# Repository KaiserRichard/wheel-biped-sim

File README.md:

# Wheel-biped simulation

A wheel-legged biped robot built three ways before any motor turns: **MuJoCo** physics, a **MATLAB Simscape Multibody** model, and the robot's own **KiCad 9 electronics**. Two five-bar legs each end in a driven wheel; the robot balances like an inverted pendulum, drives, turns, changes height and jumps.

*Simulation only: the CAD robot at an assumed 8.5 kg clearing an 8 cm obstacle in MuJoCo.*

This project builds on Trần Nguyên Bình's [DM-jump](https://github.com/nguyenbinh-shark/DM-jump) (MIT) and [dmBots/wheel-legged](https://github.com/dmBots/wheel-legged) (MIT). It is a personal refactor and extension: the concept and scenarios come from that work, and the code here was rewritten and reorganized. CAD meshes are not included. AI coding tools were used heavily in building it; the author reviewed and is responsible for all content. See [NOTICE.md](NOTICE.md).

## Simulation

Click any clip for the full MP4. All clips are played back from simulation runs, not footage of a real robot.

<table>
<tr>
<td align="center"><br>Simscape Multibody: full 16 s mission</td>
<td align="center"><br>PPO vs LQR: recovery from a 40° tilt</td>
<td align="center"><br>CAD model in MuJoCo</td>
</tr>
<tr>
<td align="center"><br>Stand and reject a push</td>
<td align="center"><br>Drive</td>
<td align="center"><br>Turn</td>
</tr>
<tr>
<td align="center"><br>Change leg height</td>
<td align="center"><br>Jump</td>
<td align="center"><br>Clear an 8 cm obstacle</td>
</tr>
<tr>
<td align="center"><br>8.5 kg: one-sided ramp</td>
<td align="center"><br>8.5 kg: 0.245 m drop</td>
<td align="center"><br>2 ms extra delay: the first controller falls</td>
</tr>
<tr>
<td align="center"><br>Firmware in the loop: <a href="docs/studies/figure-8-path-tracking.md">figure-8 path tracking</a></td>
<td align="center"><br>Firmware in the loop: <a href="docs/studies/lateral-push-low-friction.md">30 N push on a slippery floor</a></td>
<td></td>
</tr>
<tr>
<td align="center"><br>Firmware in the loop: <a href="docs/studies/push-window.md">push window, worst pitch 9.3° → 1.4°</a></td>
<td align="center"><br>Firmware in the loop: <a href="docs/studies/grip-aware-braking.md">grip-aware braking, falls 37/96 → 0/96</a></td>
<td></td>
</tr>
</table>

The full clip list, the MATLAB figures and the control story are in [docs/DETAILS.md](docs/DETAILS.md).

## Electronics

Three boards designed in KiCad 9 for a 6S battery (18.0–25.2 V). Design only: not fabricated or powered. Sources, schematic PDFs and check reports: [hardware/](hardware/README.md).

<table>
<tr>
<th>6S power and monitor board</th>
<th>STM32H723 control board</th>
<th>Motor power board</th>
</tr>
<tr>
<td align="center"></td>
<td align="center"></td>
<td align="center"></td>
</tr>
<tr>
<td align="center"></td>
<td align="center"></td>
<td align="center"></td>
</tr>
<tr>
<td>Input protection, 5 V buck rails for the Raspberry Pi and auxiliary loads, power monitoring and e-stop status. KiCad 9, ERC/DRC clean.</td>
<td>MCU with three CAN buses to the joint and wheel motors, USB to the Pi and an IMU sensor on SPI. KiCad 9, ERC/DRC clean.</td>
<td>Contactors, precharge, brake chopper and safety latch for the motor bus. KiCad 9, rev 2 schematic ERC clean; views are of the earlier layout.</td>
</tr>
</table>

Renders show archived layouts; the newest power and control revisions are listed in [hardware/README.md](hardware/README.md).

## What's inside

| Area | What it is | Read more |
| --- | --- | --- |
| MuJoCo model | Five-bar kinematics, controller and scenarios with a CPU parity test | [docs/PROJECT.md](docs/PROJECT.md) |
| Simscape model | Multibody robot with contact, six drives on a battery bus and sensor models; 16 s mission, reproducible | [docs/studio/m14-delay-robustness.md](docs/studio/m14-delay-robustness.md) |
| Control and estimation | Delay-aware LQR, gyro-bias estimator, wheel-loss feedforward, safe stop, optional PPO helper | [docs/evidence/README.md](docs/evidence/README.md) |
| Firmware | Portable C firmware with host tests and firmware-in-the-loop runs against MuJoCo | [firmware/README.md](firmware/README.md) |
| Electronics | KiCad 9 sources, schematic PDFs, ERC/DRC reports, BOM | [hardware/README.md](hardware/README.md) |
| Log tools | One telemetry format for simulation and hardware; synthetic log import and identification rehearsal | [docs/studies/log-format.md](docs/studies/log-format.md), [analyses/logsysid](analyses/logsysid/README.md) |
| Perception and SLAM | Dataset-free perception scripts and an RGB-D SLAM launch kit | [perception/README.md](perception/README.md), [slam/README.md](slam/README.md) |
| Studies | Sensitivity, contact, timestep and sim-to-real studies | [docs/studies/](docs/studies/), [sim-to-real checklist](docs/sim-to-real/sim-to-real-checklist.md) |

## Quick start

Use Python with NumPy, SciPy, MuJoCo 3.3.7, and pytest. These commands were run on CPU:

```bash
export PYTHONDONTWRITEBYTECODE=1
python check.py
python -m pytest -q -p no:cacheprovider
python models/generate.py
python scripts/stand.py --seed 0
```

More commands (log tools, log import rehearsal, project layout) are in [docs/DETAILS.md](docs/DETAILS.md).

## Status

Everything here is simulation or design: no board has been built and no motor has been powered. Results and limits, including the failures: [docs/RESULTS.md](docs/RESULTS.md).

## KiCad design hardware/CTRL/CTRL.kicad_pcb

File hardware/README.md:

**Tóm tắt [FROM FILE / COMPUTED].** Bản mới nhất là AUX rev5 và CTRL rev4; hình bên dưới thuộc các bản lưu trước đó.

# Current public revisions

[FROM FILE / COMPUTED] [Revision evidence](../docs/evidence/hardware-control-board-revision.md).

| Revision | Editable source | Schematic | Checks |
| --- | --- | --- | --- |
| AUX rev5 | [Project](AUX/wbr_power.kicad_pro) | [PDF](AUX/schematic.pdf) | [ERC](AUX/checks/erc.json), [DRC](AUX/checks/drc.json) |
| CTRL rev4 | [Project](CTRL/CTRL.kicad_pro) | [PDF](CTRL/schematic.pdf) | [ERC](CTRL/checks/erc.json), [DRC](CTRL/checks/drc.json) |

[UNKNOWN] Both boards are design-only and require bench confirmation. The renders below show the earlier archived revisions.

# Wheel-biped electronics in KiCad 9

| 6S auxiliary power board | STM32H723 control board |
| --- | --- |
|  |  |
| [Top](../media/hardware/power-board-top.png) · [Bottom](../media/hardware/power-board-bottom.png) · [KiCad project](power-board/wbr_power.kicad_pro) · [Schematic PDF](power-board/schematic.pdf) | [Top](../media/hardware/control-board-top.png) · [Bottom](../media/hardware/control-board-bottom.png) · [KiCad project](control-board/control_board.kicad_pro) · [Schematic PDF](control-board/schematic.pdf) |

## Power board v3

**FROM FILE / COMPUTED** · The power board takes a fused auxiliary branch from a **6S, 18.0–25.2 V** pack. It combines input protection, independent 5.1 V Pi and 5.0 V auxiliary buck rails, power monitoring, and probe points. The stop-status circuit reports the status of an external loop. KiCad 9.0.9 found 0 ERC errors or warnings and 0 DRC errors, warnings, unconnected items or schematic-parity findings. [ERC summary](power-board/checks/erc.json) · [DRC summary](power-board/checks/drc.json)

## Control board v2

**FROM FILE / COMPUTED** · The STM32H723 board takes its own branch from the same **6S, 18.0–25.2 V** design supply and has onboard logic regulation. It connects to the motor drives over CAN, reads the onboard IMU sensor over SPI, and exchanges commands and telemetry with the Pi 5 over USB. KiCad 9.0.9 found 0 ERC errors or warnings and 0 DRC errors, warnings, unconnected items or schematic-parity findings. [ERC summary](control-board/checks/erc.json) · [DRC summary](control-board/checks/drc.json)

## Motor power board

[Top](../media/hardware/motor-power-board-top.png) · [KiCad project](motor-power-board/motor_power.kicad_pro) · [Schematic PDF](motor-power-board/schematic.pdf) · [ERC report](motor-power-board/checks/ERC.rpt) · [DRC report](motor-power-board/checks/DRC.rpt) · [BOM](motor-power-board/bom.csv)

**FROM FILE / COMPUTED** · The four-layer motor power board (96 × 99 mm, 70 µm outer copper, 35 µm inner copper, 1.60 mm stackup) manages the **6S, 18.0–25.2 V** traction feeder for all six motor drives. It controls two external series normally-open contactors with mirror-contact feedback, differential precharge through an external 3.0 Ω resistor (~0.85 V differential gate and hardware timer), a link-powered 1.5 Ω regenerative brake chopper (26.48 V rising / 25.99 V falling, ~27.95 V persistent overvoltage monitor), a 330 Ω passive bleeder, a dual-channel wired and supervised-radio safety relay latch with monitored reset, a logic permit and status connector to the STM32H723 control board, and an optional DNP feeder shunt and current monitor. KiCad 9.0.9 found 0 ERC errors, 0 ERC warnings, 0 PCB DRC violations, 0 unconnected pads, 0 footprint errors and 0 schematic parity issues across the six-page schematic.

**FROM FILE / UNKNOWN** · This board is **design-only, not fabricated**. No parts were purchased and the board has never been built or powered. Inrush current, precharge sequencing, contactor release and single-fault weld detection, clamp thermal margin and remote drive terminal overshoot, and wired/radio e-stop timing all require bench verification on a supported fixture.

## System connections

**FROM FILE** · The diagram shows the proposed system interfaces. The power board's auxiliary 5.0 V output is for a separate auxiliary load.

```mermaid
flowchart LR
    Pack["6S battery · 18.0–25.2 V"] -->|Fused auxiliary tap| Power["Power board"]
    Pack -->|Separate fused branch| Control["STM32H723 control board"]
    Power -->|5.1 V| Pi["Raspberry Pi 5"]
    Power -->|5.0 V| Aux["Auxiliary rail"]
    Sensor["IMU sensor"] -->|SPI| Control
    Control <-->|USB| Pi
    Control <-->|CAN command and feedback| Motors["Motor drives"]
    Pack -->|Independent traction branch| Motors
```

**FROM FILE / UNKNOWN** · These are **design-only learning boards**. No parts were purchased and the boards were never fabricated or powered. ERC and DRC check the configured schematic and layout rules. Thermal margin, load transients and e-stop behavior still require physical verification. Some component bodies are unavailable in the 3D library and appear as pads or outlines.

**FROM FILE** · The power board builds on the owner's earlier private **Edge AI Smart Power Module** project, carrying forward its input protection, buck rails, power monitoring and test-point organization. The control board follows the MCU pin and peripheral map in Trần Nguyên Bình's MIT-licensed **DM-jump CtrlBoard-H7** configuration. Library licensing and attribution are documented in [NOTICE.md](../NOTICE.md).

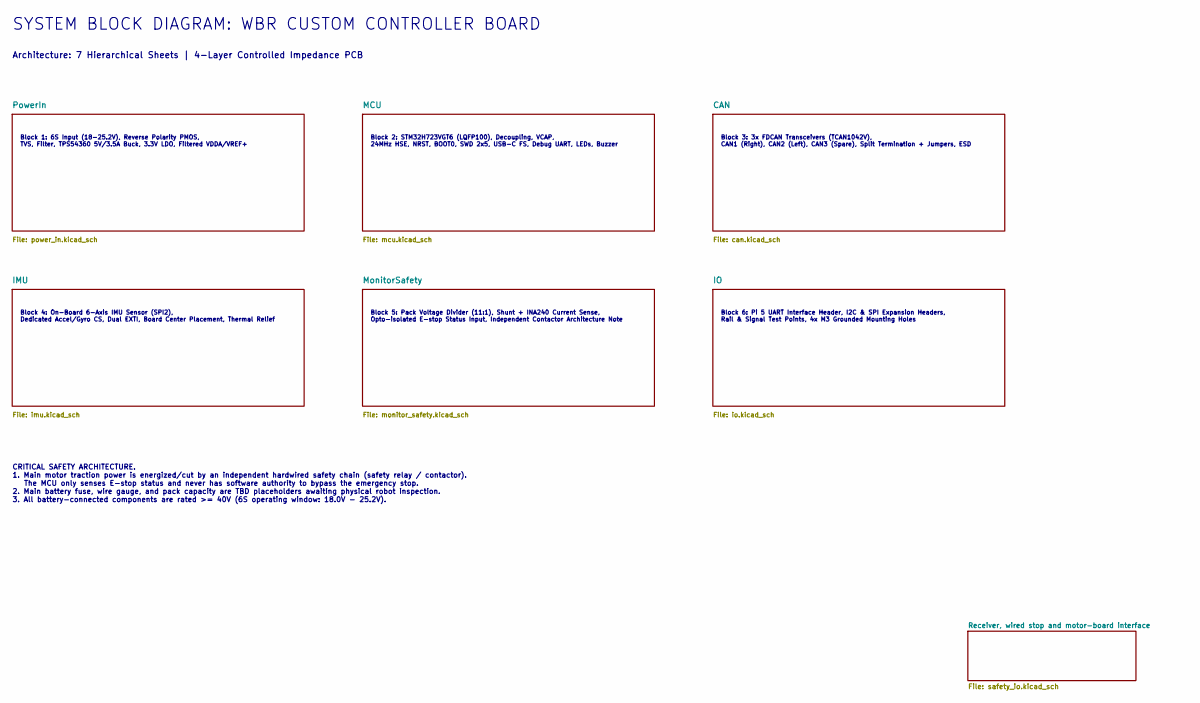
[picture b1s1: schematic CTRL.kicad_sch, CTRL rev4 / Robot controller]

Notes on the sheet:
SYSTEM BLOCK DIAGRAM: WBR CUSTOM CONTROLLER BOARD
Architecture: 7 Hierarchical Sheets | 4-Layer Controlled Impedance PCB
Block 1: 6S Input (18-25.2V), Reverse Polarity PMOS, TVS, Filter, TPS54360 5V/3.5A Buck, 3.3V LDO, Filtered VDDA/VREF+
Block 2: STM32H723VGT6 (LQFP100), Decoupling, VCAP, 24MHz HSE, NRST, BOOT0, SWD 2x5, USB-C FS, Debug UART, LEDs, Buzzer
Block 3: 3x FDCAN Transceivers (TCAN1042V), CAN1 (Right), CAN2 (Left), CAN3 (Spare), Split Termination + Jumpers, ESD
Block 4: On-Board 6-Axis IMU Sensor (SPI2), Dedicated Accel/Gyro CS, Dual EXTI, Board Center Placement, Thermal Relief
Block 5: Pack Voltage Divider (11:1), Shunt + INA240 Current Sense, Opto-isolated E-stop Status Input, Independent Contactor Architecture Note
Block 6: Pi 5 UART Interface Header, I2C & SPI Expansion Headers, Rail & Signal Test Points, 4x M3 Grounded Mounting Holes
CRITICAL SAFETY ARCHITECTURE. 1. Main motor traction power is energized/cut by an independent hardwired safety chain (safety relay / contactor). The MCU only senses E-stop status and never has software authority to bypass the emergency stop. 2. Main battery fuse, wire gauge, and pack capacity are T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

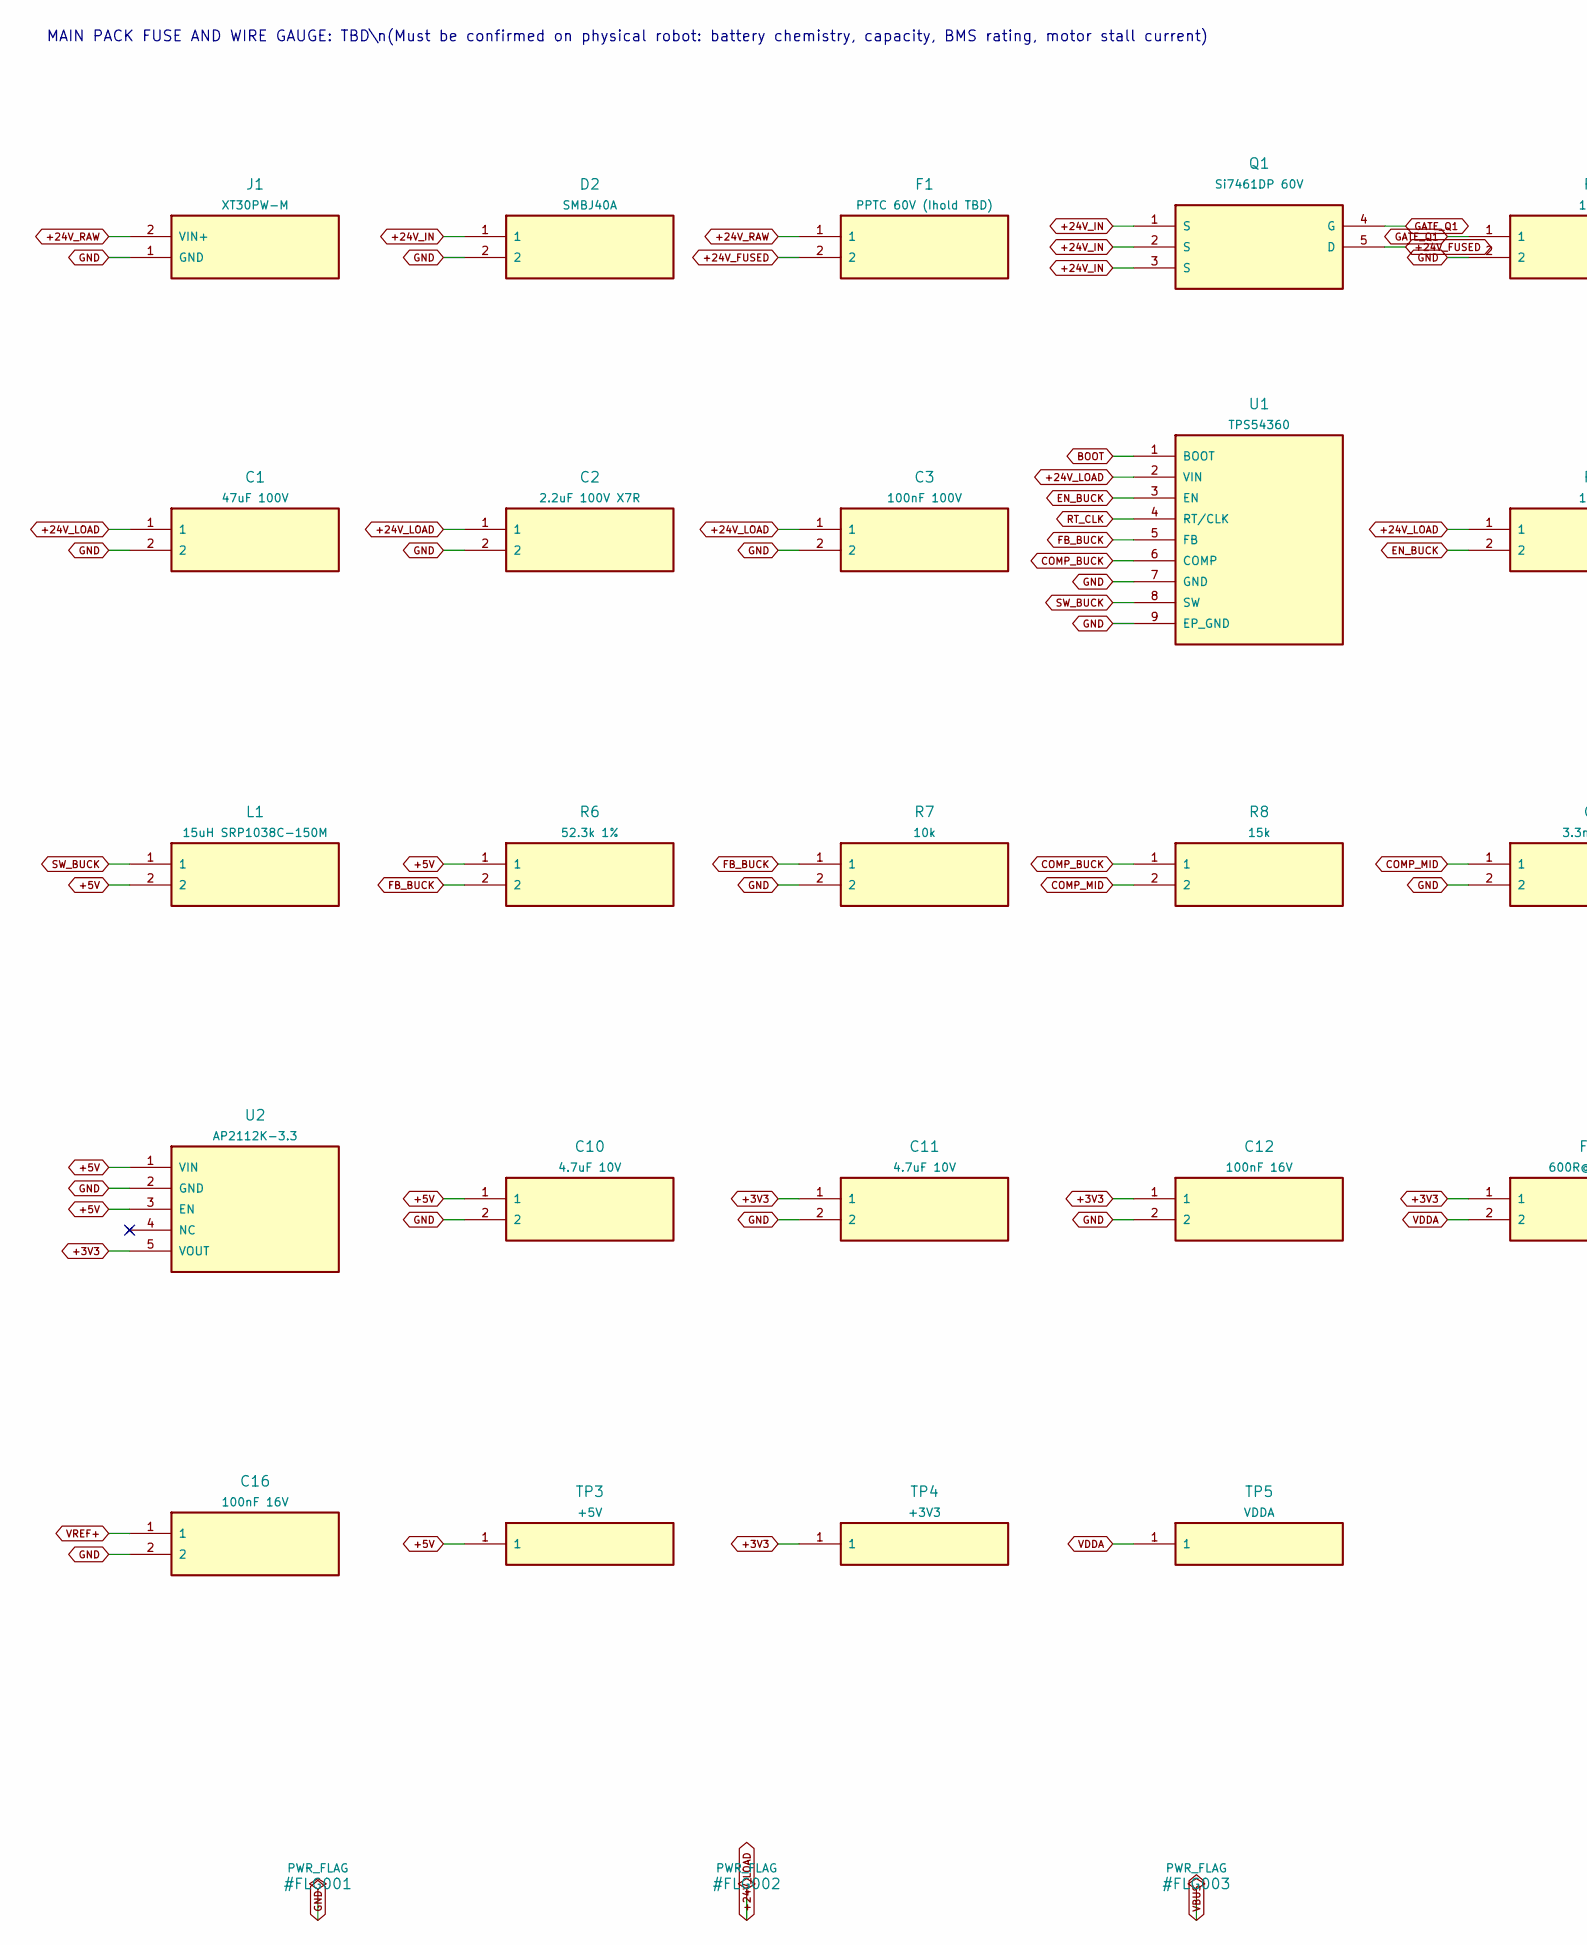
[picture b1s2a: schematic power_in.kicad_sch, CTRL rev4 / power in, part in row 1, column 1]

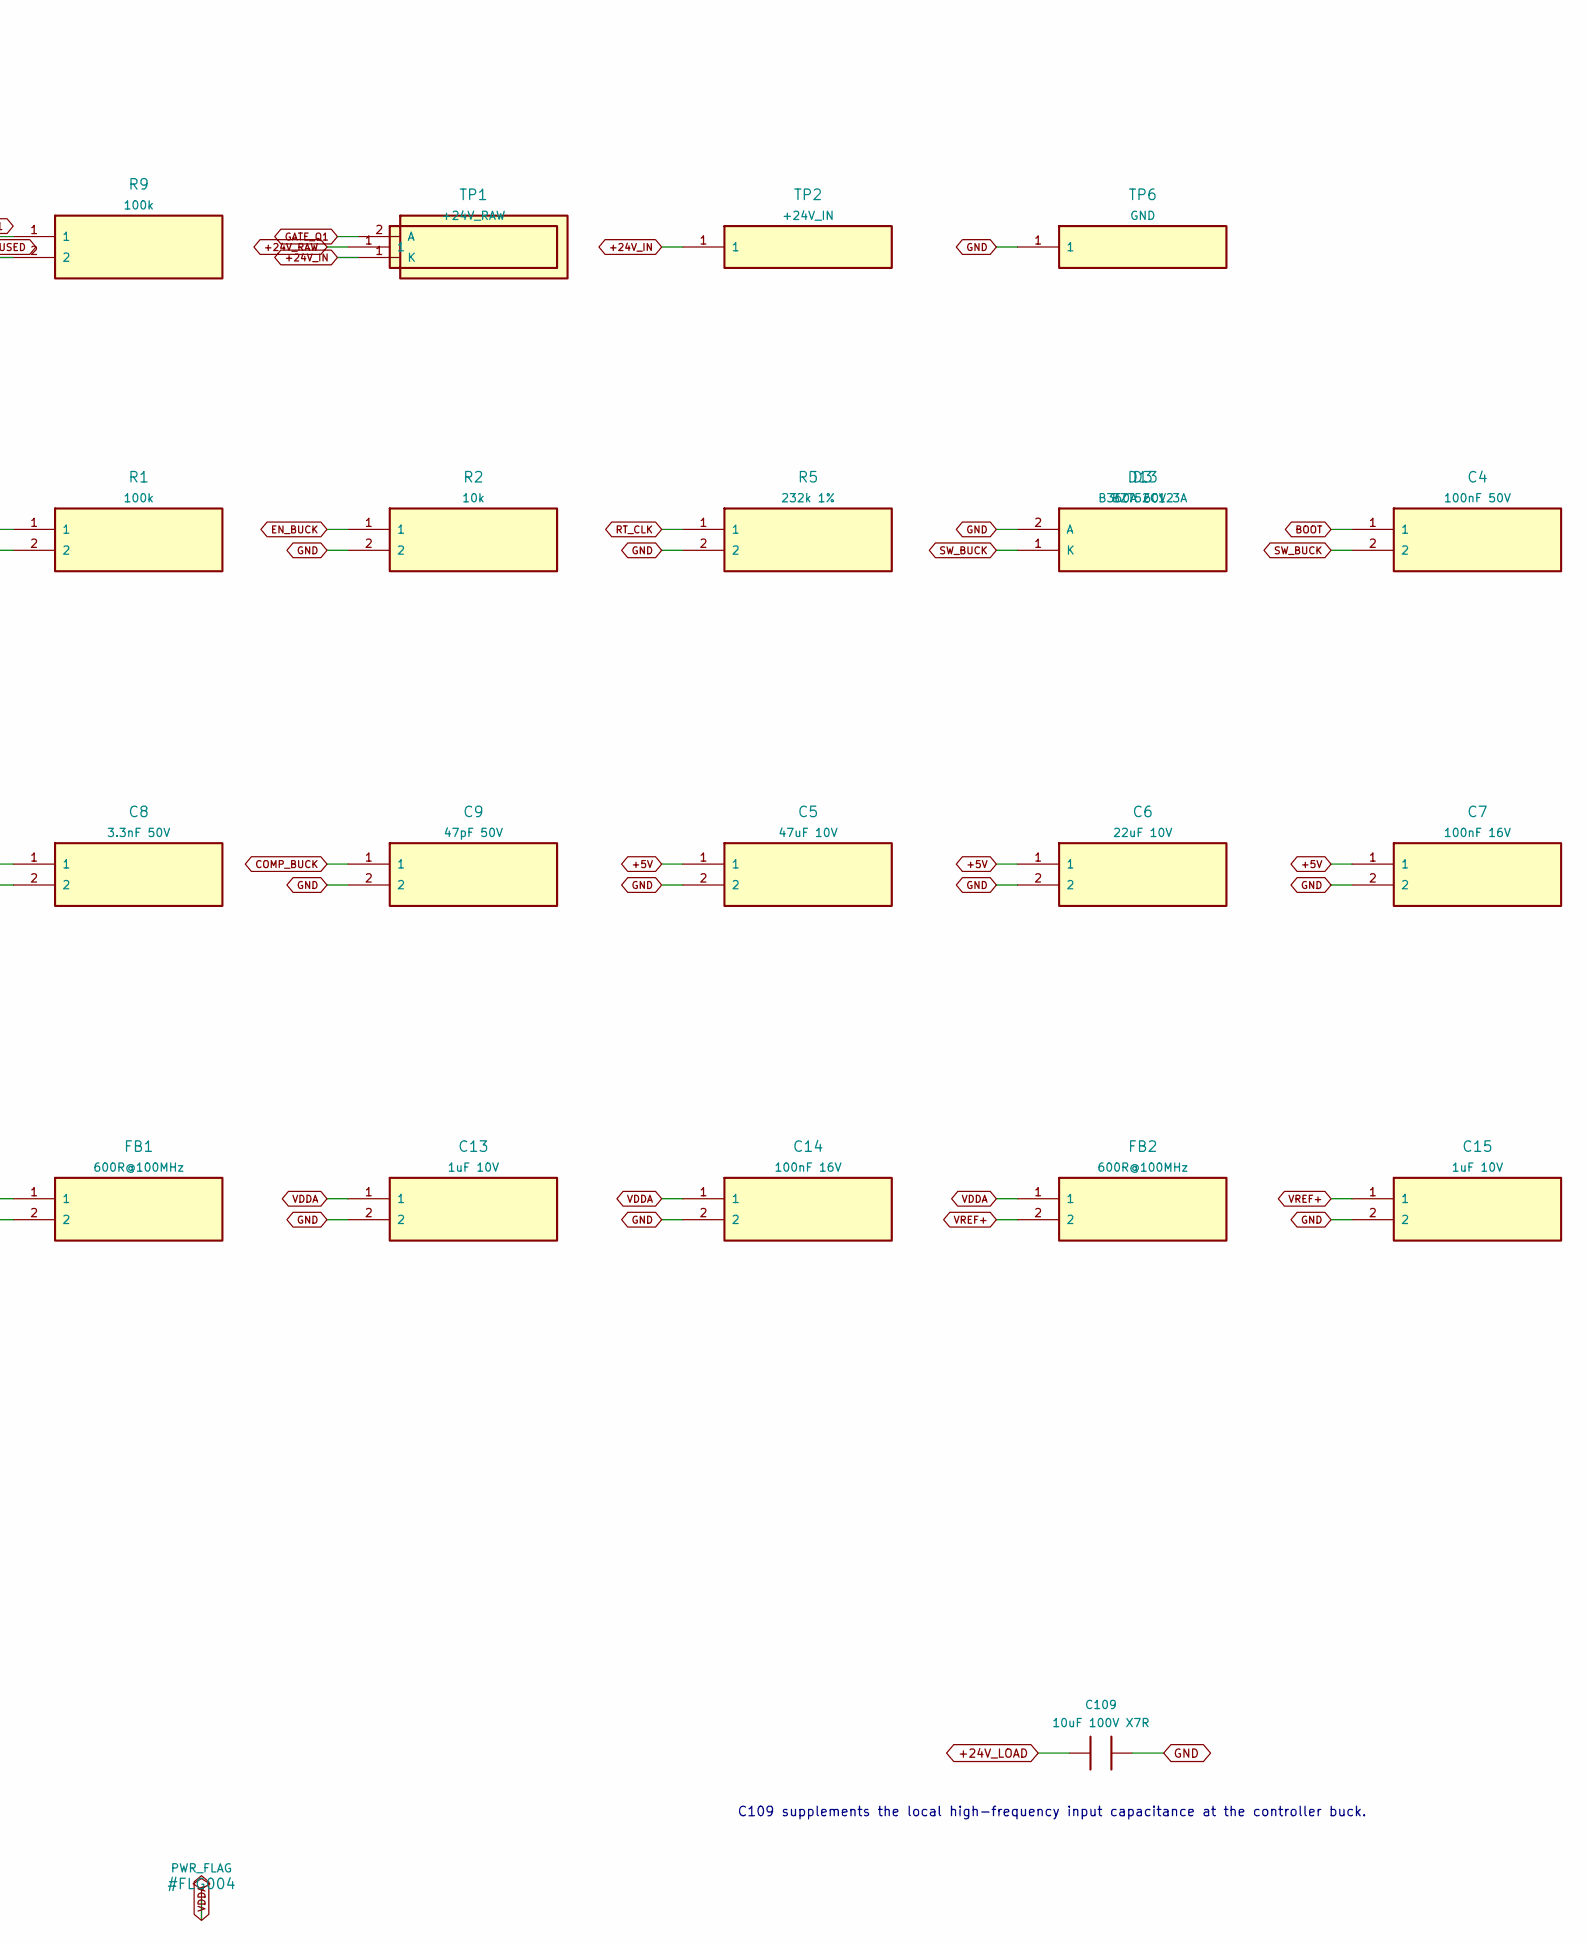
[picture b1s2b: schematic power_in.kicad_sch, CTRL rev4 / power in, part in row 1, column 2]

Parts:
C1: 47uF 100V; CP_Elec_10x10; MPN UUX2A470MNL1GS
C2: 2.2uF 100V X7R; C_0805_2012Metric; MPN C2012X7R2A225K125AC
C3: 100nF 100V; C_0805_2012Metric
C4: 100nF 50V; C_0805_2012Metric
C5: 47uF 10V; CP_Elec_6.3x5.8
C6: 22uF 10V; C_0805_2012Metric
C7, C12, C14, C16: 100nF 16V; C_0805_2012Metric
C8: 3.3nF 50V; C_0805_2012Metric
C9: 47pF 50V; C_0805_2012Metric
C10, C11: 4.7uF 10V; C_0805_2012Metric
C13, C15: 1uF 10V; C_0805_2012Metric
C109: 10uF 100V X7R; C_1210_3225Metric; MPN C3225X7R2A106K250AC
D2: SMBJ40A; D_SMB; MPN SMBJ40A
D3: B360A 60V 3A; D_SMA
D13: BZT52C12; D_SOD-123
F1: PPTC 60V (Ihold TBD); Fuse_1812_4532Metric
FB1, FB2: 600R@100MHz; L_0805_2012Metric
J1: XT30PW-M; AMASS_XT30PW-M_1x02_P2.50mm_Horizontal
L1: 15uH SRP1038C-150M; L_Bourns_SRP1038C_10.0x10.0mm
Q1: Si7461DP 60V; PowerPAK_SO-8_Single
R1, R9: 100k; R_0805_2012Metric
R2, R7: 10k; R_0805_2012Metric
R5: 232k 1%; R_0805_2012Metric
R6: 52.3k 1%; R_0805_2012Metric
R8: 15k; R_0805_2012Metric
TP1: +24V_RAW; TestPoint_Pad_D1.5mm
TP2: +24V_IN; TestPoint_Pad_D1.5mm
TP3: +5V; TestPoint_Pad_D1.5mm
TP4: +3V3; TestPoint_Pad_D1.5mm
TP5: VDDA; TestPoint_Pad_D1.5mm
TP6: GND; TestPoint_Pad_D1.5mm
U1: TPS54360; SOIC-8-1EP_3.9x4.9mm_P1.27mm_EP2.41x3.3mm
U2: AP2112K-3.3; SOT-23-5

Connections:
+3V3: C11.1, C12.1, FB1.1, TP4.1, U2.5 (VOUT); also elsewhere on the board
+5V: C5.1, C6.1, C7.1, C10.1, L1.2, R6.1, TP3.1, U2.1 (VIN), U2.3 (EN); also elsewhere on the board
+24V_FUSED: F1.2, Q1.5 (D)
+24V_IN: D2.1, D13.1 (K), Q1.1 (S), Q1.2 (S), Q1.3 (S), TP2.1; also elsewhere on the board
+24V_LOAD: C1.1, C2.1, C3.1, C109.1, R1.1, U1.2 (VIN); also elsewhere on the board
+24V_RAW: F1.1, J1.2 (VIN+), TP1.1
BOOT: C4.1, U1.1 (BOOT)
COMP_BUCK: C9.1, R8.1, U1.6 (COMP)
COMP_MID: C8.1, R8.2
EN_BUCK: R1.2, R2.1, U1.3 (EN)
FB_BUCK: R6.2, R7.1, U1.5 (FB)
GATE_Q1: D13.2 (A), Q1.4 (G), R9.1
GND: C1.2, C2.2, C3.2, C5.2, C6.2, C7.2, C8.2, C9.2, C10.2, C11.2, C12.2, C13.2, C14.2, C15.2, C16.2, C109.2, D2.2, D3.2 (A), J1.1 (GND), R2.2, R5.2, R7.2, R9.2, TP6.1, U1.7 (GND), U1.9 (EP_GND), U2.2 (GND); also elsewhere on the board
RT_CLK: R5.1, U1.4 (RT/CLK)
SW_BUCK: C4.2, D3.1 (K), L1.1, U1.8 (SW)
VDDA: C13.1, C14.1, FB1.2, FB2.1, TP5.1; also elsewhere on the board
VREF+: C15.1, C16.1, FB2.2; also elsewhere on the board

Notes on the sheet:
MAIN PACK FUSE AND WIRE GAUGE: TBD\n(Must be confirmed on physical robot: battery chemistry, capacity, BMS rating, motor stall current)
C109 supplements the local high-frequency input capacitance at the controller buck.

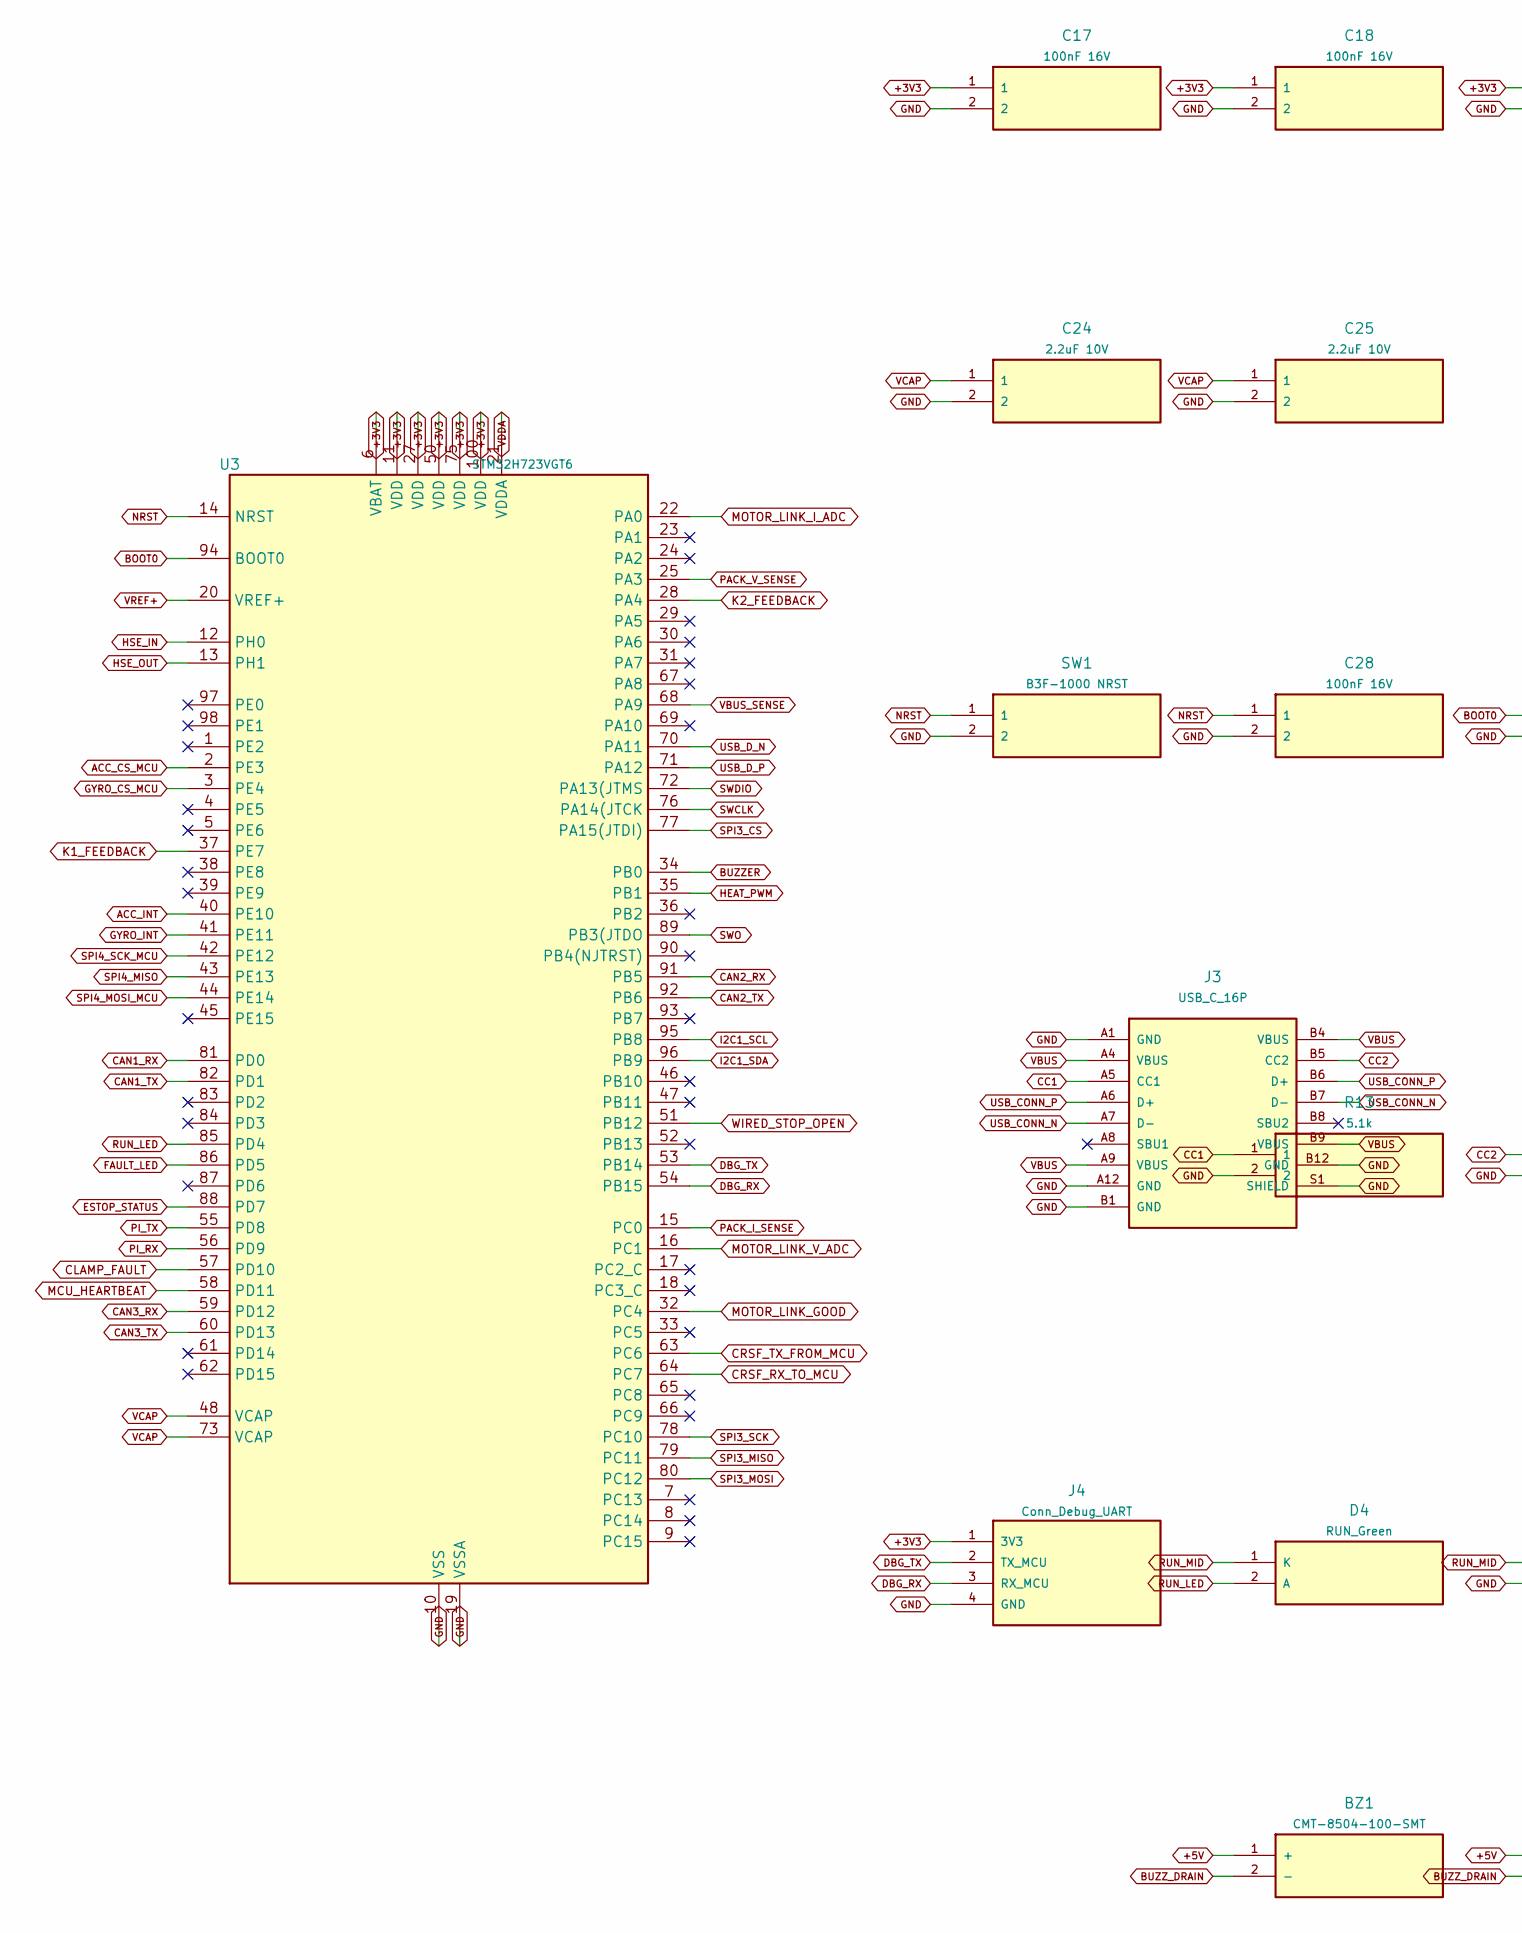
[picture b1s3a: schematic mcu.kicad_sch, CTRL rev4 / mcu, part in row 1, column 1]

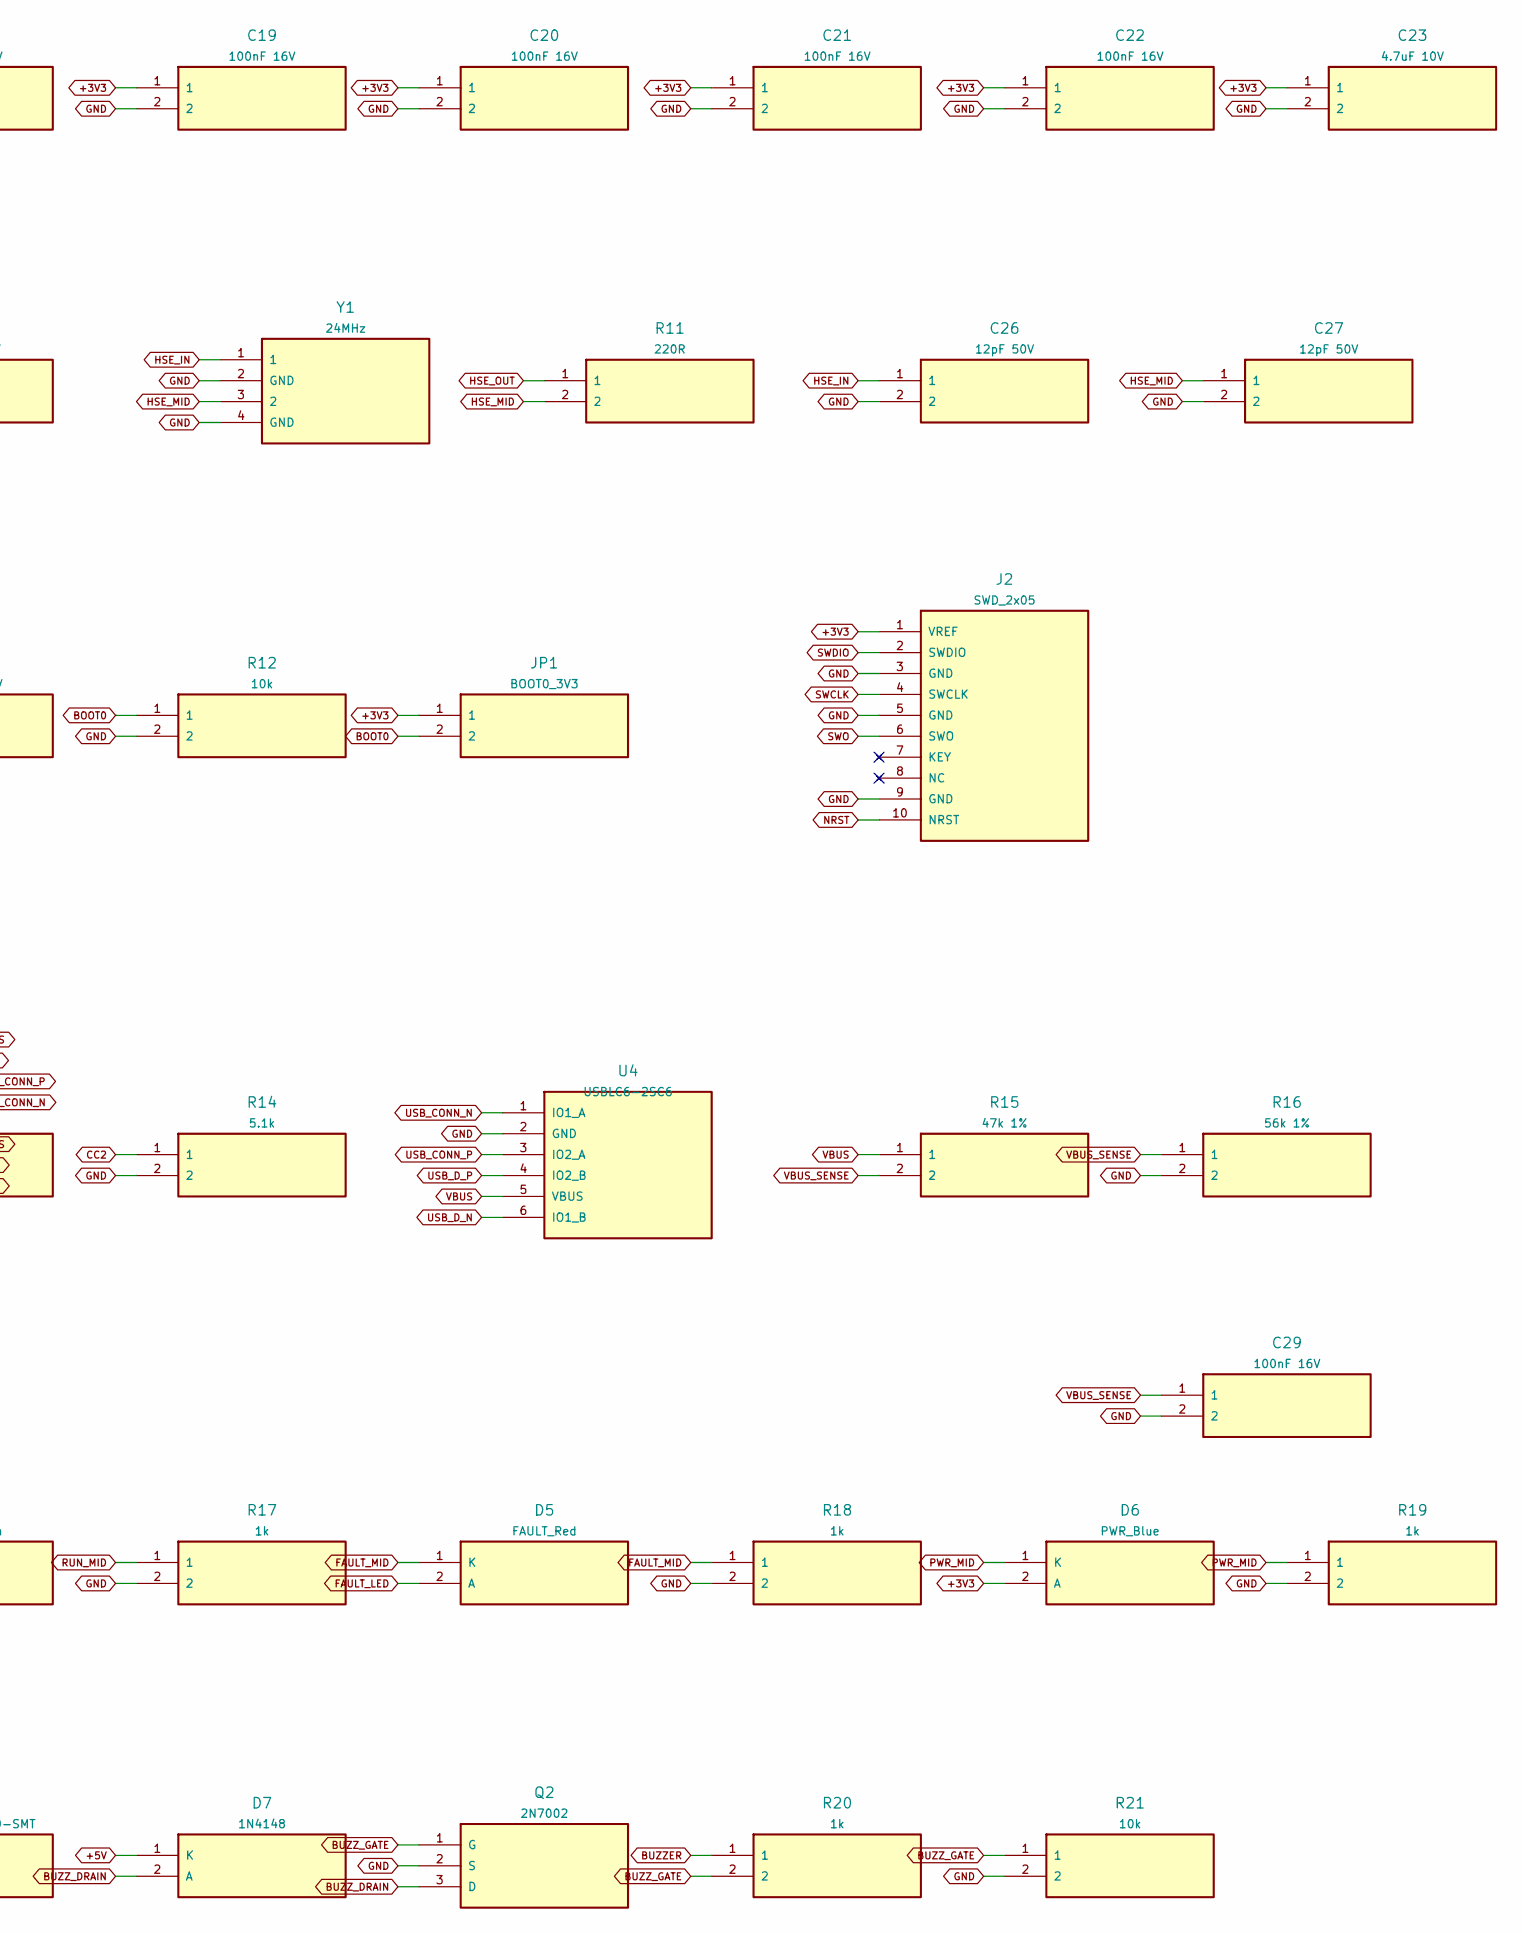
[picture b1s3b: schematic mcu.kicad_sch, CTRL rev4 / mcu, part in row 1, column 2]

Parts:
BZ1: CMT-8504-100-SMT; MagneticBuzzer_CUI_CMT-8504-100-SMT
C17, C18, C19, C20, C21, C22, C28, C29: 100nF 16V; C_0805_2012Metric
C23: 4.7uF 10V; C_0805_2012Metric
C24, C25: 2.2uF 10V; C_0805_2012Metric
C26, C27: 12pF 50V; C_0805_2012Metric
D4: RUN_Green; LED_0805_2012Metric
D5: FAULT_Red; LED_0805_2012Metric
D6: PWR_Blue; LED_0805_2012Metric
D7: 1N4148; D_SOD-123
J2: SWD_2x05; PinHeader_2x05_P1.27mm_Vertical_SMD
J3: USB_C_16P; USB_C_Receptacle_HRO_TYPE-C-31-M-12
J4: Conn_Debug_UART; PinHeader_1x04_P2.54mm_Vertical
JP1: BOOT0_3V3; PinHeader_1x02_P2.54mm_Vertical
Q2: 2N7002; SOT-23
R11: 220R; R_0805_2012Metric
R12, R21: 10k; R_0805_2012Metric
R13, R14: 5.1k; R_0805_2012Metric
R15: 47k 1%; R_0805_2012Metric
R16: 56k 1%; R_0805_2012Metric
R17, R18, R19, R20: 1k; R_0805_2012Metric
SW1: B3F-1000 NRST; SW_TH_Tactile_Omron_B3F-100x
U3: STM32H723VGT6; LQFP-100_14x14mm_P0.5mm
U4: USBLC6-2SC6; SOT-23-6
Y1: 24MHz; Crystal_SMD_3225-4Pin_3.2x2.5mm

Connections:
+3V3: C17.1, C18.1, C19.1, C20.1, C21.1, C22.1, C23.1, D6.2 (A), J2.1 (VREF), J4.1 (3V3), JP1.1, U3.6 (VBAT), U3.11 (VDD), U3.27 (VDD), U3.50 (VDD), U3.75 (VDD), U3.100 (VDD); also elsewhere on the board
+5V: BZ1.1 (+), D7.1 (K); also elsewhere on the board
ACC_CS_MCU: U3.2 (PE3); also elsewhere on the board
ACC_INT: U3.40 (PE10); also elsewhere on the board
BOOT0: JP1.2, R12.1, U3.94 (BOOT0); also elsewhere on the board
BUZZER: R20.1, U3.34 (PB0)
BUZZ_DRAIN: BZ1.2 (-), D7.2 (A), Q2.3 (D)
BUZZ_GATE: Q2.1 (G), R20.2, R21.1
CAN1_RX: U3.81 (PD0); also elsewhere on the board
CAN1_TX: U3.82 (PD1); also elsewhere on the board
CAN2_RX: U3.91 (PB5); also elsewhere on the board
CAN2_TX: U3.92 (PB6); also elsewhere on the board
CAN3_RX: U3.59 (PD12); also elsewhere on the board
CAN3_TX: U3.60 (PD13); also elsewhere on the board
CC1: J3.A5 (CC1), R13.1
CC2: J3.B5 (CC2), R14.1
CLAMP_FAULT: U3.57 (PD10); also elsewhere on the board
CRSF_RX_TO_MCU: U3.64 (PC7); also elsewhere on the board
CRSF_TX_FROM_MCU: U3.63 (PC6); also elsewhere on the board
DBG_RX: J4.3 (RX_MCU), U3.54 (PB15)
DBG_TX: J4.2 (TX_MCU), U3.53 (PB14)
ESTOP_STATUS: U3.88 (PD7); also elsewhere on the board
FAULT_LED: D5.2 (A), U3.86 (PD5)
FAULT_MID: D5.1 (K), R18.1
GND: C17.2, C18.2, C19.2, C20.2, C21.2, C22.2, C23.2, C24.2, C25.2, C26.2, C27.2, C28.2, C29.2, J2.3 (GND), J2.5 (GND), J2.9 (GND), J3.A1 (GND), J3.A12 (GND), J3.B1 (GND), J3.B12 (GND), J3.S1 (SHIELD), J4.4 (GND), Q2.2 (S), R12.2, R13.2, R14.2, R16.2, R17.2, R18.2, R19.2, R21.2, SW1.2, U3.10 (VSS), U3.19 (VSSA), U3.26 (VSS), U3.49 (VSS), U3.74 (VSS), U3.99 (VSS), U4.2 (GND), Y1.2 (GND), Y1.4 (GND); also elsewhere on the board
GYRO_CS_MCU: U3.3 (PE4); also elsewhere on the board
GYRO_INT: U3.41 (PE11); also elsewhere on the board
HEAT_PWM: U3.35 (PB1); also elsewhere on the board
HSE_IN: C26.1, U3.12 (PH0), Y1.1
HSE_MID: C27.1, R11.2, Y1.3 (2)
HSE_OUT: R11.1, U3.13 (PH1)
I2C1_SCL: U3.95 (PB8); also elsewhere on the board
I2C1_SDA: U3.96 (PB9); also elsewhere on the board
K1_FEEDBACK: U3.37 (PE7); also elsewhere on the board
K2_FEEDBACK: U3.28 (PA4); also elsewhere on the board
MCU_HEARTBEAT: U3.58 (PD11); also elsewhere on the board
MOTOR_LINK_GOOD: U3.32 (PC4); also elsewhere on the board
MOTOR_LINK_I_ADC: U3.22 (PA0); also elsewhere on the board
MOTOR_LINK_V_ADC: U3.16 (PC1); also elsewhere on the board
NRST: C28.1, J2.10 (NRST), SW1.1, U3.14 (NRST); also elsewhere on the board
PACK_I_SENSE: U3.15 (PC0); also elsewhere on the board
PACK_V_SENSE: U3.25 (PA3); also elsewhere on the board
PI_RX: U3.56 (PD9); also elsewhere on the board
PI_TX: U3.55 (PD8); also elsewhere on the board
PWR_MID: D6.1 (K), R19.1
RUN_LED: D4.2 (A), U3.85 (PD4)
RUN_MID: D4.1 (K), R17.1
SPI3_CS: U3.77 (PA15(JTDI)); also elsewhere on the board
SPI3_MISO: U3.79 (PC11); also elsewhere on the board
SPI3_MOSI: U3.80 (PC12); also elsewhere on the board
SPI3_SCK: U3.78 (PC10); also elsewhere on the board
SPI4_MISO: U3.43 (PE13); also elsewhere on the board
SPI4_MOSI_MCU: U3.44 (PE14); also elsewhere on the board
SPI4_SCK_MCU: U3.42 (PE12); also elsewhere on the board
SWCLK: J2.4 (SWCLK), U3.76 (PA14(JTCK)
SWDIO: J2.2 (SWDIO), U3.72 (PA13(JTMS)
SWO: J2.6 (SWO), U3.89 (PB3(JTDO)
USB_CONN_N: J3.A7 (D-), J3.B7 (D-), U4.1 (IO1_A)
USB_CONN_P: J3.A6 (D+), J3.B6 (D+), U4.3 (IO2_A)
USB_D_N: U3.70 (PA11), U4.6 (IO1_B)
USB_D_P: U3.71 (PA12), U4.4 (IO2_B)
VBUS: J3.A4 (VBUS), J3.A9 (VBUS), J3.B4 (VBUS), J3.B9 (VBUS), R15.1, U4.5 (VBUS)
VBUS_SENSE: C29.1, R15.2, R16.1, U3.68 (PA9)
VCAP: C24.1, C25.1, U3.48 (VCAP), U3.73 (VCAP); also elsewhere on the board
VDDA: U3.21 (VDDA); also elsewhere on the board
VREF+: U3.20 (VREF+); also elsewhere on the board
WIRED_STOP_OPEN: U3.51 (PB12); also elsewhere on the board
